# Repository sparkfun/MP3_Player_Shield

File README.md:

SparkFun MP3 Player Shield
==========================

[*SparkFun MP3 Player Shield (DEV-2660)*](https://www.sparkfun.com/products/12660)

The MP3 Player Shield has a microSD socket, VS1053 decoder IC and all the supporting circuitry to be able to decode and play MP3s from an Arduino.

Repository Contents
-------------------

* **/Documentation** - Data sheets, additional product information
* **/Firmware** - Multiple examples of how to read MP3 files and send them to the VS1053.
* **/Hardware** - All Eagle design files (.brd, .sch)
* **/Production** - Production panel files (.brd)

Documentation
--------------
* **[Hookup Guide](https://learn.sparkfun.com/tutorials/mp3-player-shield-hookup-guide-v15)** - Basic hookup guide for the Mp3 Shield.
* **[SparkFun Fritzing repo](https://github.com/sparkfun/Fritzing_Parts)** - Fritzing diagrams for SparkFun products.
* **[SparkFun 3D Model repo](https://github.com/sparkfun/3D_Models)** - 3D models of SparkFun products. 

Product Versions
----------------
* [DEV-09736](https://www.sparkfun.com/products/retired/9736)- Version 1.0. Retired. 
* [DEV-10628](https://www.sparkfun.com/products/retired/10628)- Version 1.3. Retired. 
* [DEV-12660](https://www.sparkfun.com/products/12660) - Version 1.5. Current. 

Version History
---------------
* [v1.3](https://github.com/sparkfun/MP3_Player_Shield/tree/V_1.3) - Version 1.3 GitHub files. Retired. 
* [v1.5](https://github.com/sparkfun/MP3_Player_Shield/tree/V_1.5) - Version 1.5 GitHub files. Current. 

License Information
-------------------

This product is _**open source**_! 

Please review the LICENSE.md file for license information. 

If you have any questions or concerns on licensing, please contact techsupport@sparkfun.com.

Distributed as-is; no warranty is given.

- Your friends at SparkFun.

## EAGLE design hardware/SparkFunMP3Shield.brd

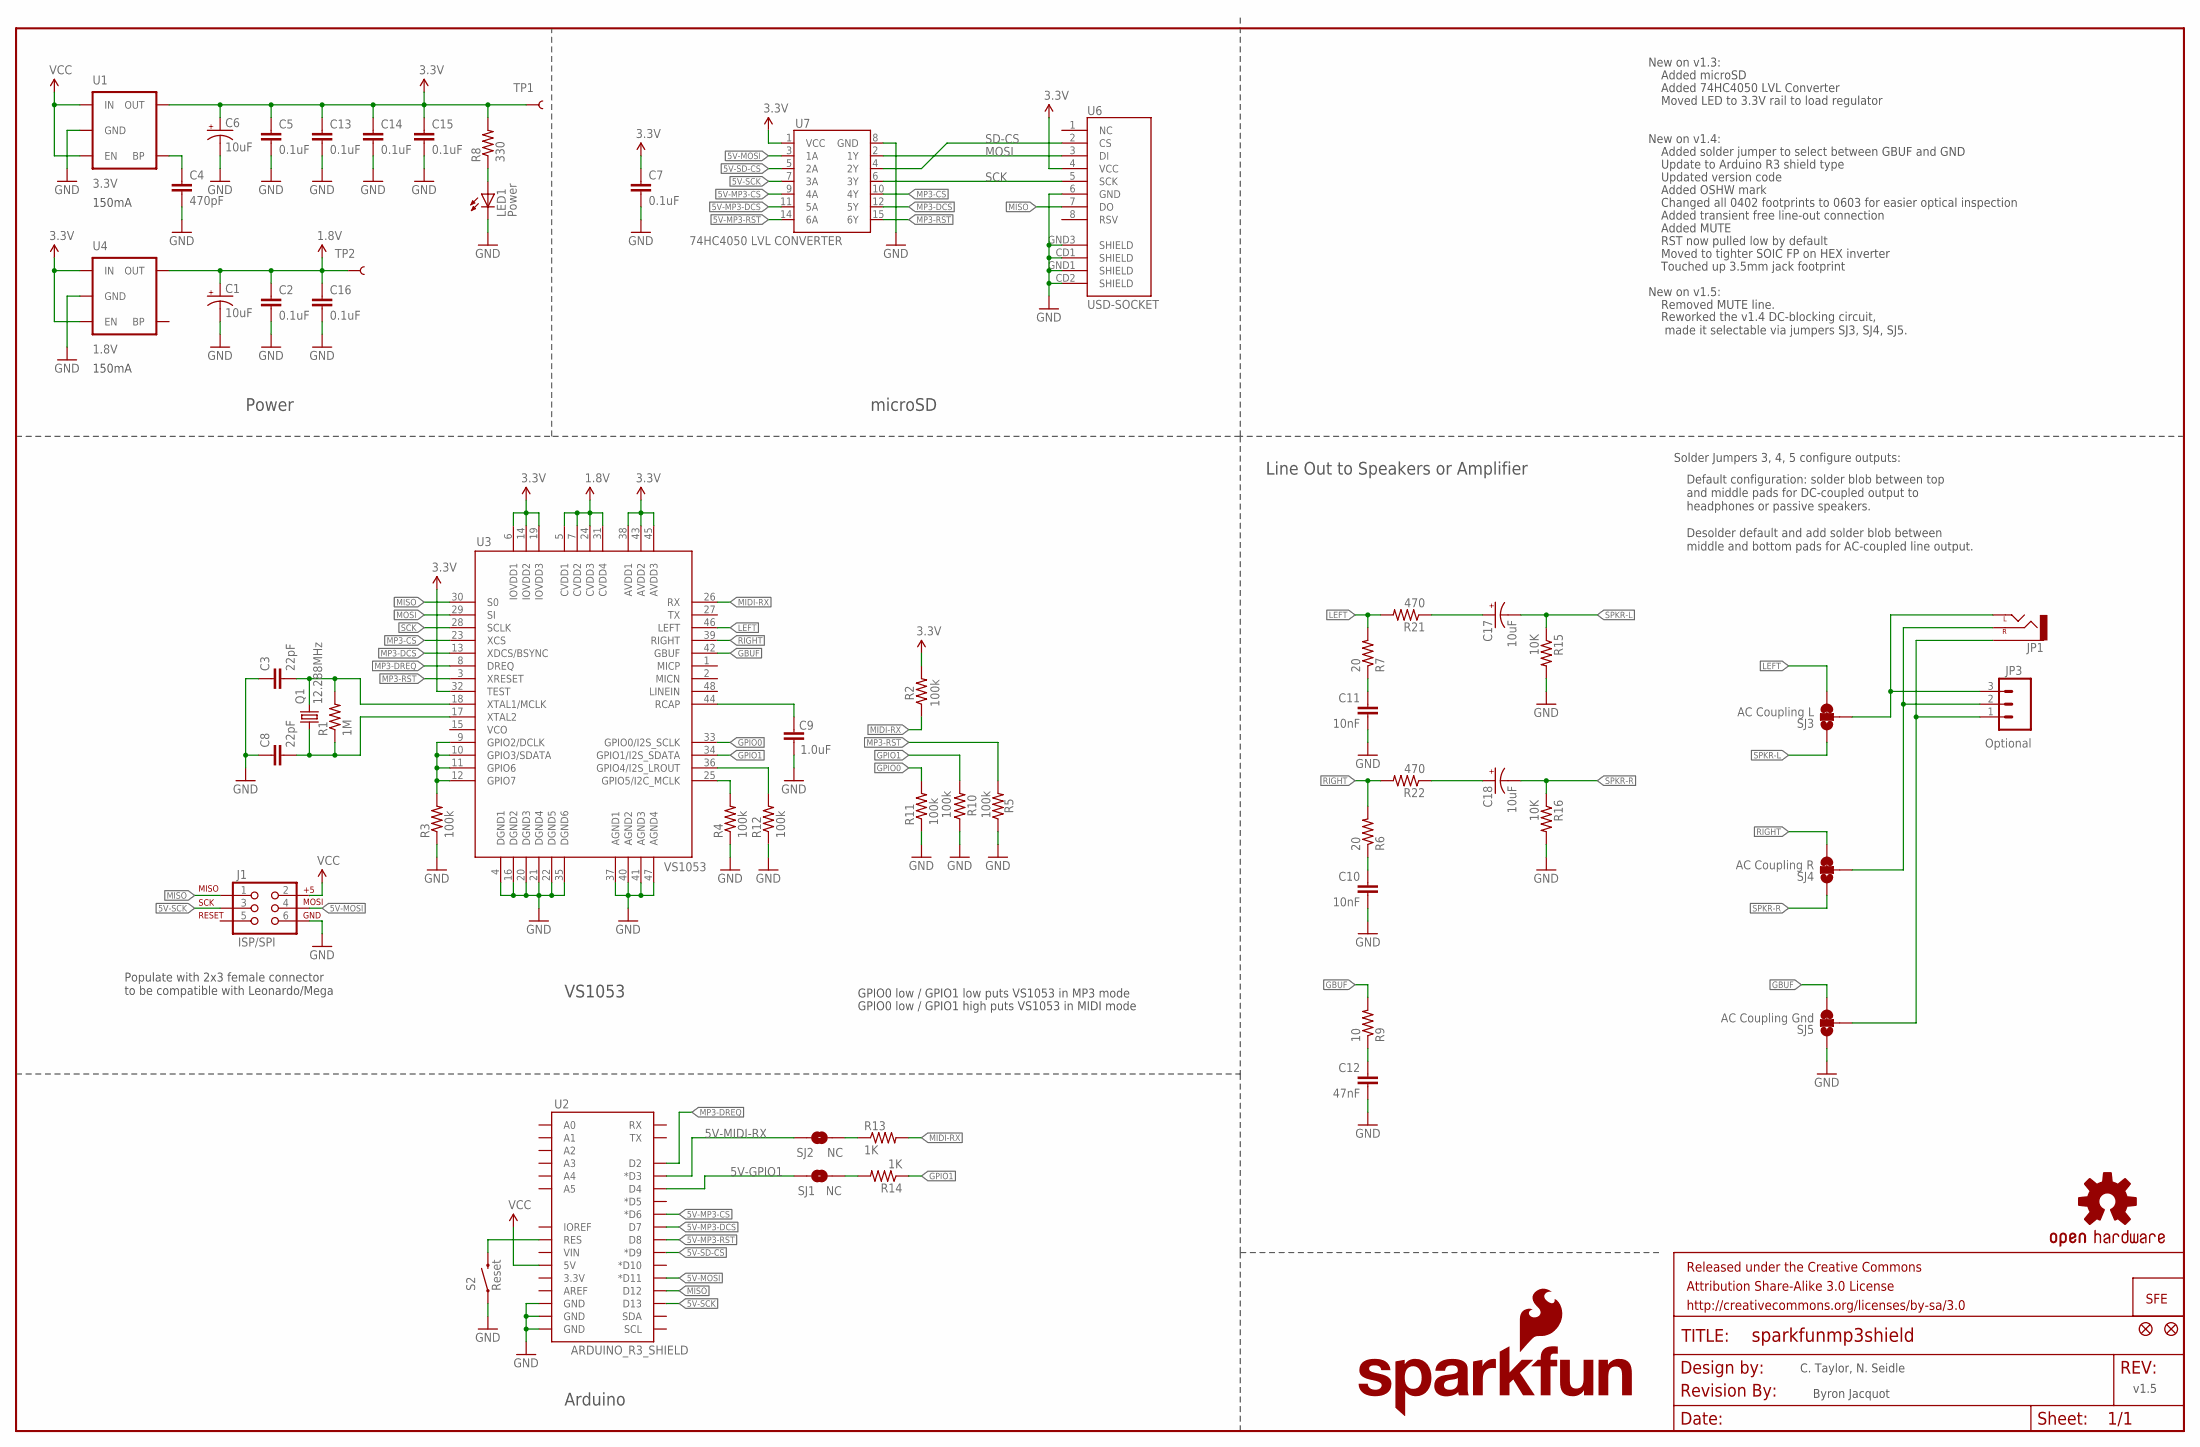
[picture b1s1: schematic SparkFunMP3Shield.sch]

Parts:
C1, C6, C17, C18: 10uF; EIA3216
C2, C5, C7, C13, C14, C15, C16: 0.1uF; 0603-CAP
C3, C8: 22pF; 0603-CAP
C4: 470pF; 0603-CAP
C9: 1.0uF; 0603-CAP
C10, C11: 10nF; 0603-CAP
C12: 47nF; 0603-CAP
FRAME1: FRAME-LEDGER; CREATIVE_COMMONS
J1: ISP/SPI; 2X3
JP1: AUDIO-JACKSMD2; AUDIO-JACK-3.5MM-SMD
JP3: Optional; 1X03
LED1: Power; LED-0603
LOGO1: OSHW-LOGOS; OSHW-LOGO-S
LOGO2: SFE_LOGO_NAME_FLAME.1_INCH; SFE_LOGO_NAME_FLAME_.1
Q1: 12.288MHz; CRYSTAL-SMD-5X3
R1: 1M; 0603-RES
R2, R3, R4, R5, R10, R11, R12: 100k; 0603-RES
R6, R7: 20; 0603-RES
R8: 330; 0603-RES
R9: 10; 0603-RES
R13, R14: 1K; 0603-RES
R15, R16: 10K; 0603-RES
R21, R22: 470; 0603-RES
S2: Reset; TACTILE_SWITCH_SMD
SJ1, SJ2: NC; SJ_2S-TRACE
SJ3: AC Coupling L; SMT-JUMPER_3_1-NC_TRACE_SILK
SJ4: AC Coupling R; SMT-JUMPER_3_1-NC_TRACE_SILK
SJ5: AC Coupling Gnd; SMT-JUMPER_3_1-NC_TRACE_SILK
TP1, TP2: TEST-POINT3X5; PAD.03X.05
U1: 3.3V; SOT23-5
U2: ARDUINO_R3_SHIELD; UNO_R3_SHIELD
U3: VS1053; LQFP-48
U4: 1.8V; SC70
U6: USD-SOCKET; MICRO-SD-SOCKET-PP
U7: 74HC4050 LVL CONVERTER; SO016
U$1: REVISION
U$4, U$5: FIDUCIAL1X2; FIDUCIAL-1X2
U$8: LOGO-SFENEW; SFE-NEW-WEBLOGO

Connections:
1.8V: C1.A (+), C2.1, C16.1, TP2.P$1, U3.5 (CVDD1), U3.7 (CVDD2), U3.24 (CVDD3), U3.31 (CVDD4), U4.5 (OUT)
3.3V: C5.1, C6.A (+), C7.1, C13.1, C14.1, C15.1, R2.2, R8.2, TP1.P$1, U1.5 (OUT), U3.6 (IOVDD1), U3.14 (IOVDD2), U3.19 (IOVDD3), U3.32 (TEST), U3.38 (AVDD1), U3.43 (AVDD2), U3.45 (AVDD3), U4.1 (IN), U4.3 (EN), U6.4 (VCC), U7.1 (VCC)
5V-GPIO1: SJ1.2, U2.D4
5V-MIDI-RX: SJ2.1, U2.D3 (*D3)
5V-MOSI: J1.4, U2.D11 (*D11), U7.3 (1A)
5V-MP3-CS: U2.D6 (*D6), U7.9 (4A)
5V-MP3-DCS: U2.D7, U7.11 (5A)
5V-MP3-RST: U2.D8, U7.14 (6A)
5V-SCK: J1.3, U2.D13, U7.7 (3A)
5V-SD-CS: U2.D9 (*D9), U7.5 (2A)
ARST: S2.3 (2), U2.RES
G1: R3.2, U3.9 (GPIO2/DCLK), U3.10 (GPIO3/SDATA), U3.11 (GPIO6), U3.12 (GPIO7)
G2: R4.2, U3.25 (GPIO5/I2C_MCLK)
GBUF: R9.2, SJ5.3, U3.42 (GBUF)
GND: C1.C (-), C2.2, C3.1, C4.2, C5.2, C6.C (-), C7.2, C8.1, C9.1, C10.2, C11.2, C12.2, C13.2, C14.2, C15.2, C16.2, J1.6, LED1.C, R3.1, R4.1, R5.1, R10.1, R11.1, R12.1, R15.2, R16.2, S2.1, SJ5.1, U1.2 (GND), U2.GND@0 (GND), U2.GND@1 (GND), U2.GND@2 (GND), U3.4 (DGND1), U3.16 (DGND2), U3.20 (DGND3), U3.21 (DGND4), U3.22 (DGND5), U3.35 (DGND6), U3.37 (AGND1), U3.40 (AGND2), U3.41 (AGND3), U3.47 (AGND4), U4.2 (GND), U6.6 (GND), U6.CD1 (SHIELD), U6.CD2 (SHIELD), U6.GND1 (SHIELD), U6.GND3 (SHIELD), U7.8 (GND)
GPIO0: R11.2, U3.33 (GPIO0/I2S_SCLK)
GPIO1: R10.2, R14.1, U3.34 (GPIO1/I2S_SDATA)
GPIO4: R12.2, U3.36 (GPIO4/I2S_LROUT)
LEFT: R7.2, R21.2, SJ3.3, U3.46 (LEFT)
MIDI-RX: R2.1, R13.2, U3.26 (RX)
MISO: J1.1, U2.D12, U3.30 (S0), U6.7 (DO)
MOSI: U3.29 (SI), U6.3 (DI), U7.2 (1Y)
MP3-CS: U3.23 (XCS), U7.10 (4Y)
MP3-DCS: U3.13 (XDCS/BSYNC), U7.12 (5Y)
MP3-DREQ: U2.D2, U3.8 (DREQ)
MP3-RST: R5.2, U3.3 (XRESET), U7.15 (6Y)
unnamed: C12.1, R9.1
unnamed: C10.1, R6.1
unnamed: R14.2, SJ1.1
unnamed: C11.1, R7.1
unnamed: LED1.A, R8.1
unnamed: R13.1, SJ2.2
unnamed: C3.2, Q1.3 (2), R1.2, U3.18 (XTAL1/MCLK)
unnamed: C8.2, Q1.1, R1.1, U3.17 (XTAL2)
unnamed: JP1.SLEEVE, JP3.1, SJ5.2
unnamed: JP1.RING (RIGHT), JP3.2, SJ4.2
unnamed: JP1.TIP (LEFT), JP3.3, SJ3.2
unnamed: C18.A (+), R22.1
unnamed: C17.A (+), R21.1
unnamed: C4.1, U1.4 (BP)
RCAP: C9.2, U3.44 (RCAP)
RIGHT: R6.2, R22.2, SJ4.3, U3.39 (RIGHT)
SCK: U3.28 (SCLK), U6.5 (SCK), U7.6 (3Y)
SD-CS: U6.2 (CS), U7.4 (2Y)
SPKR-L: C17.C (-), R15.1, SJ3.1
SPKR-R: C18.C (-), R16.1, SJ4.1
VCC: J1.2, U1.1 (IN), U1.3 (EN), U2.5V

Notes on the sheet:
GPIO0 low / GPIO1 high puts VS1053 in MIDI mode
C. Taylor, N. Seidle
New on v1.3:
GPIO0 low / GPIO1 low puts VS1053 in MP3 mode
microSD
Power
Line Out to Speakers or Amplifier
Arduino
VS1053
Moved LED to 3.3V rail to load regulator
Added microSD
Added 74HC4050 LVL Converter
New on v1.4:
Added solder jumper to select between GBUF and GND
Default configuration: solder blob between top and middle pads for DC-coupled output to headphones or passive speakers. Desolder default and add solder blob between middle and bottom pads for AC-coupled line output.
Update to Arduino R3 shield type
Updated version code
Added OSHW mark
Changed all 0402 footprints to 0603 for easier optical inspection
Added transient free line-out connection
Added MUTE
Solder Jumpers 3, 4, 5 configure outputs:
150mA
v1.5
RST now pulled low by default
Populate with 2x3 female connector to be compatible with Leonardo/Mega
Moved to tighter SOIC FP on HEX inverter
Touched up 3.5mm jack footprint
Byron Jacquot
New on v1.5:
Removed MUTE line.
Reworked the v1.4 DC-blocking circuit, made it selectable via jumpers SJ3, SJ4, SJ5.

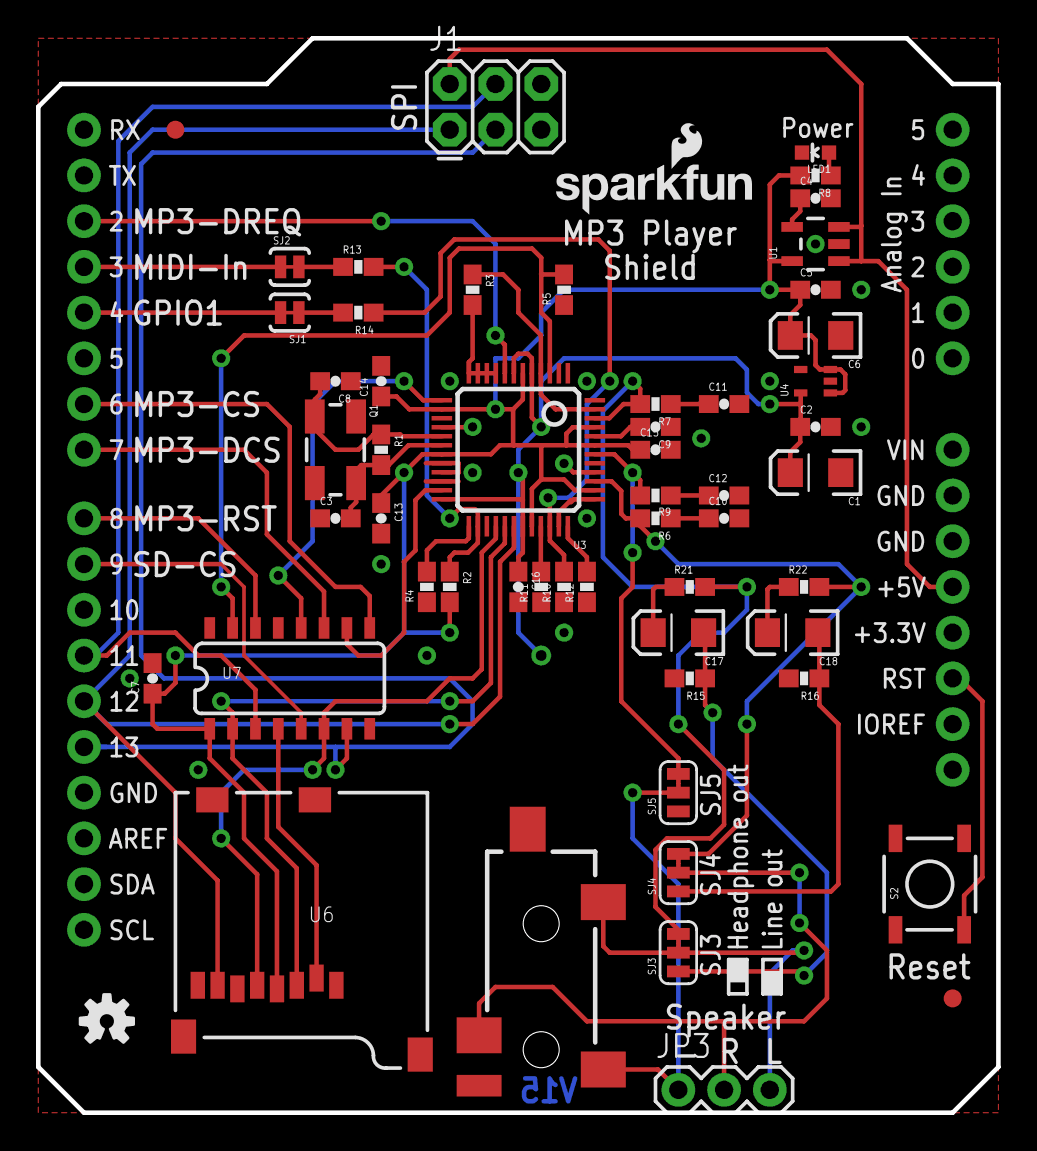
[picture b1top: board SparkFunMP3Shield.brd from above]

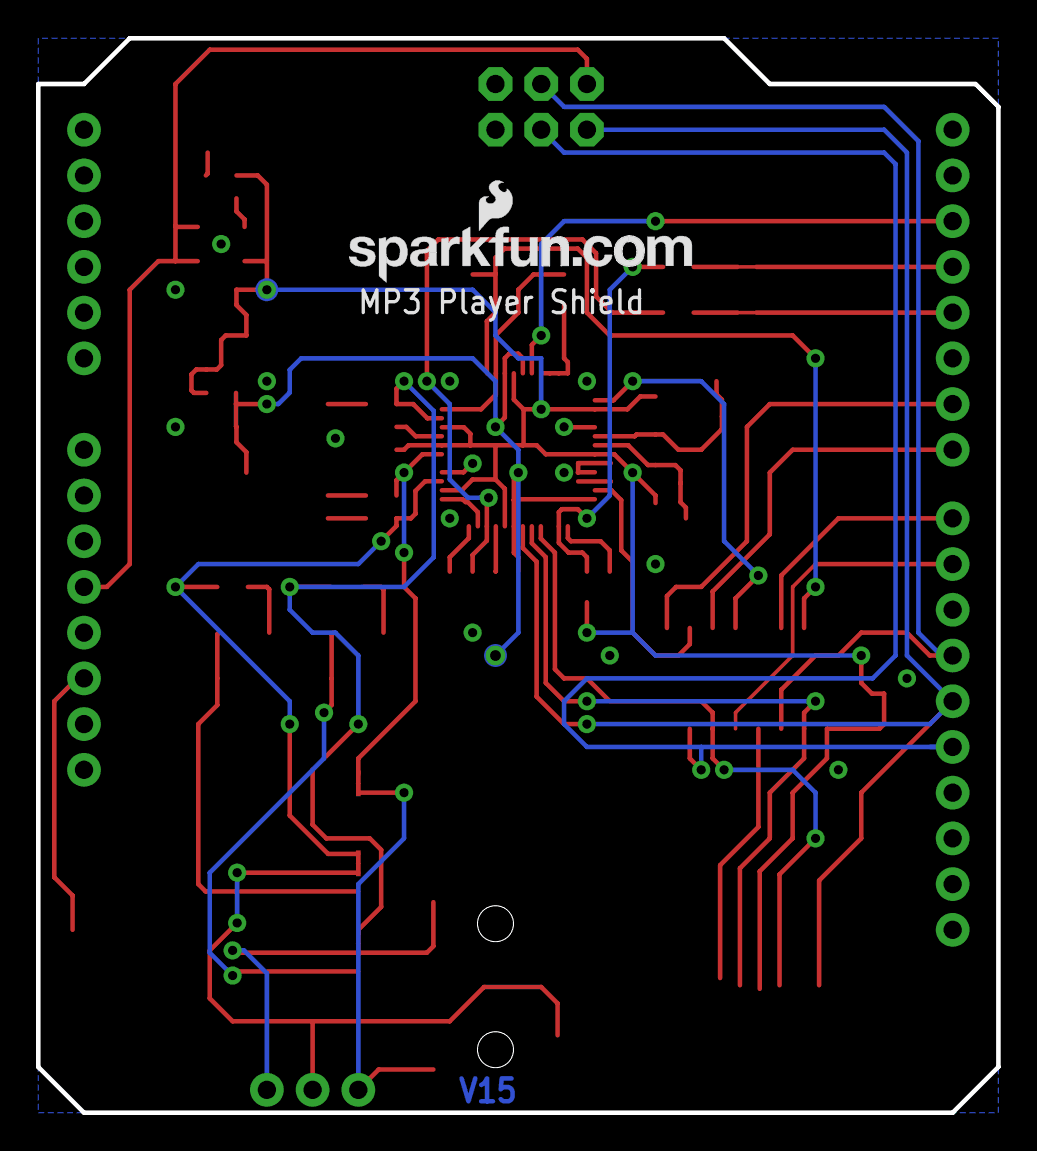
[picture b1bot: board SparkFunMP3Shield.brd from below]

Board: 2 copper layers, 53.3 x 59.7 mm, 62 parts (3 on the bottom side), 47 nets.

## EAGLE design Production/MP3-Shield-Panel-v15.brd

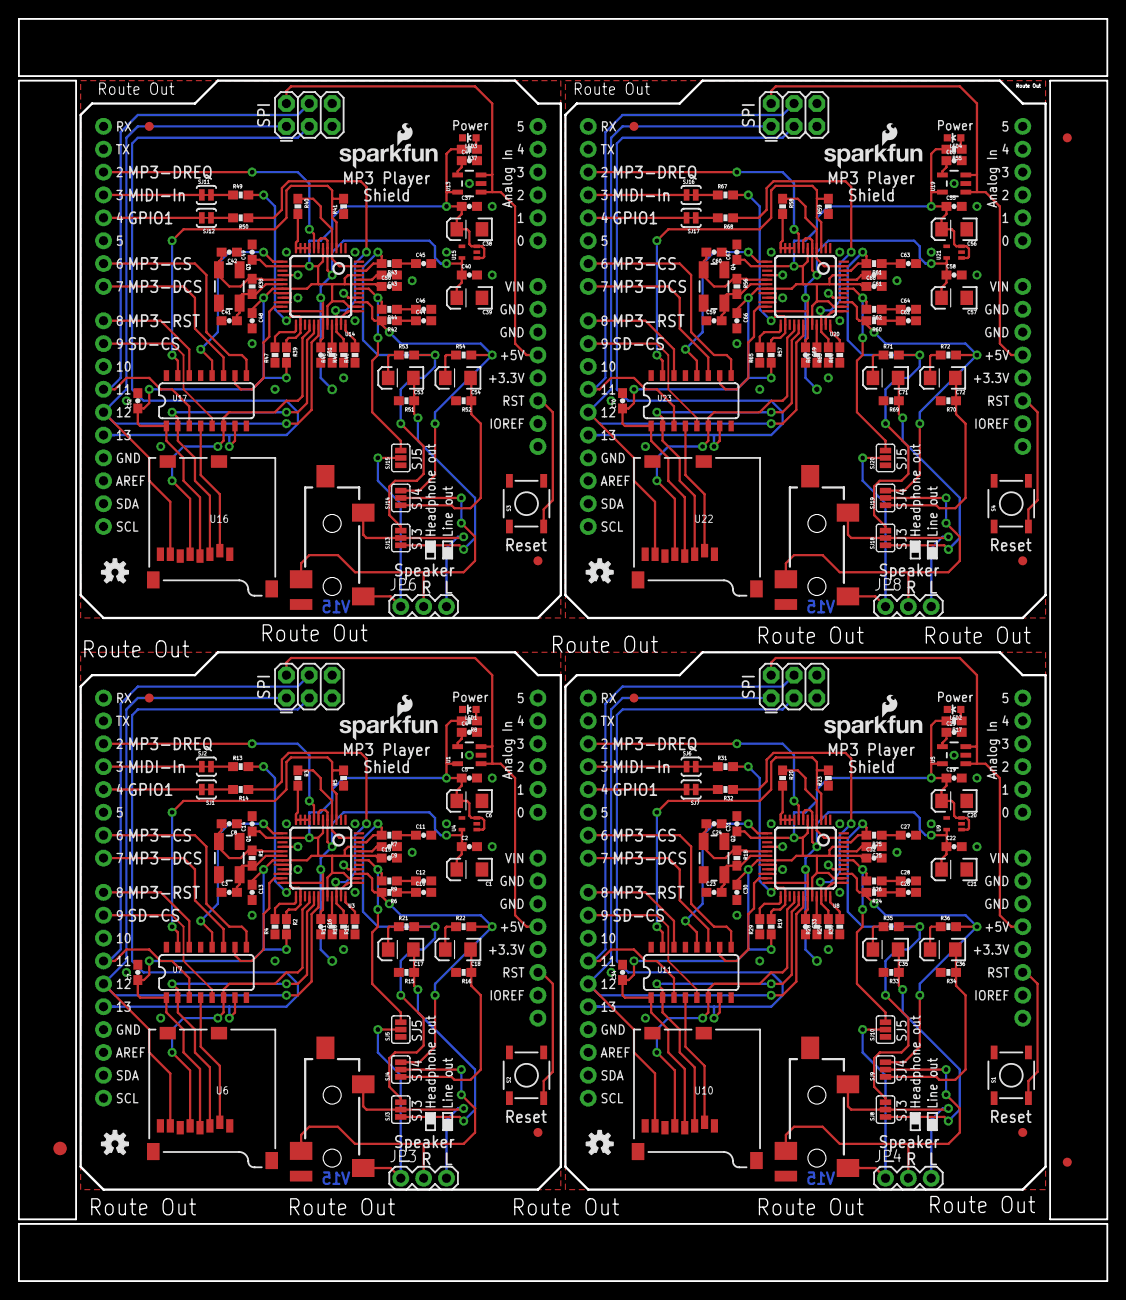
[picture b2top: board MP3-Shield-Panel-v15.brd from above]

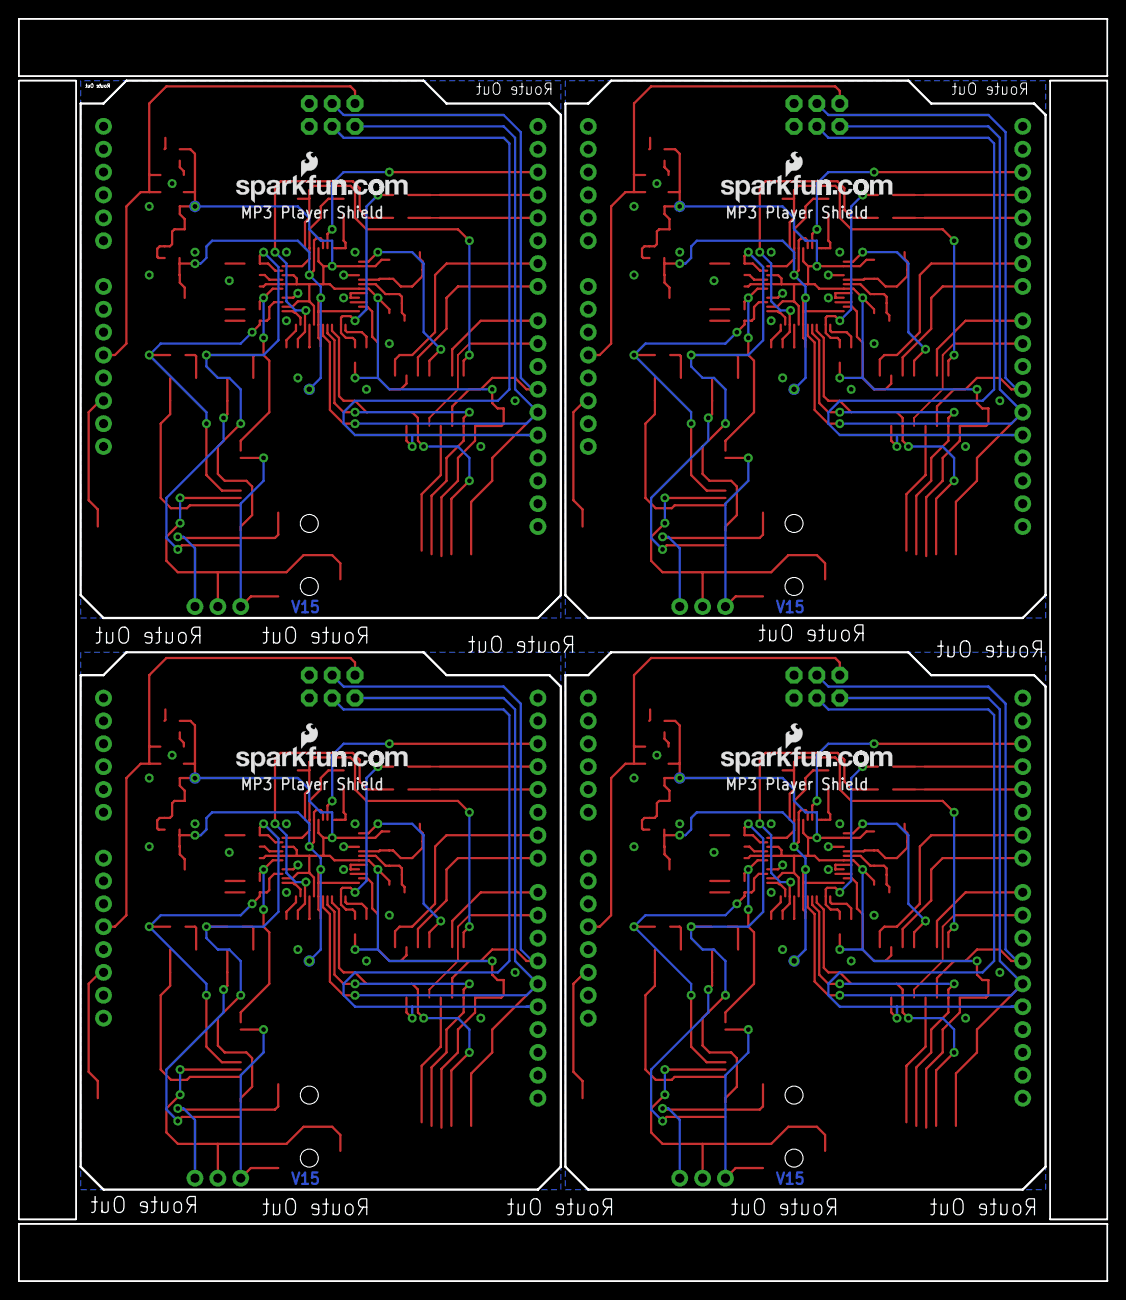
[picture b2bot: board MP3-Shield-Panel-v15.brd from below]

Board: 2 copper layers, 120.9 x 140.2 mm, 243 parts (12 on the bottom side), 188 nets.

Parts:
C1, C6, C17, C18, C20, C21, C35, C36, C38, C39, C53, C54, C56, C57, C71, C72: 10uF; EIA3216
C2, C5, C7, C13, C14, C15, C16, C19, C22, C30, C31, C32, C33, C34, C37, C40, C48, C49, C50, C51, C52, C55, C58, C66, C67, C68, C69, C70: 0.1uF; 0603-CAP
C3, C8, C23, C24, C41, C42, C59, C60: 22pF; 0603-CAP
C4, C29, C47, C65: 470pF; 0603-CAP
C9, C25, C43, C61: 1.0uF; 0603-CAP
C10, C11, C26, C27, C44, C45, C62, C63: 10nF; 0603-CAP
C12, C28, C46, C64: 47nF; 0603-CAP
E$1: FIDUCIAL-1.5X3
E$4, E$5: FIDUCIAL-1X2
J1, J2, J3, J4: ISP/SPI; 2X3
JP1, JP2, JP5, JP7: AUDIO-JACK-3.5MM-SMD
JP3, JP4, JP6, JP8: Optional; 1X03
LED1, LED2, LED3, LED4: Power; LED-0603
LOGO1, LOGO3, LOGO5, LOGO7: OSHW-LOGOS; OSHW-LOGO-S
LOGO2, LOGO4, LOGO6, LOGO8: SFE_LOGO_NAME_FLAME.1_INCH; SFE_LOGO_NAME_FLAME_.1
Q1, Q2, Q3, Q4: 12.288MHz; CRYSTAL-SMD-5X3
R1, R18, R38, R56: 1M; 0603-RES
R2, R3, R4, R5, R10, R11, R12, R19, R20, R23, R27, R28, R29, R30, R39, R40, R41, R45, R46, R47, R48, R57, R58, R59, R63, R64, R65, R66: 100k; 0603-RES
R6, R7, R24, R25, R42, R43, R60, R61: 20; 0603-RES
R8, R17, R37, R55: 330; 0603-RES
R9, R26, R44, R62: 10; 0603-RES
R13, R14, R31, R32, R49, R50, R67, R68: 1K; 0603-RES
R15, R16, R33, R34, R51, R52, R69, R70: 10K; 0603-RES
R21, R22, R35, R36, R53, R54, R71, R72: 470; 0603-RES
S1, S2, S3, S4: Reset; TACTILE_SWITCH_SMD
SJ1, SJ2, SJ6, SJ7, SJ11, SJ12, SJ16, SJ17: NC; SJ_2S-TRACE
SJ3, SJ8, SJ13, SJ18: AC Coupling L; PAD-JUMPER-3-2OF3_NC_BY_PASTE_YES_SILK_FULL_BOX
SJ4, SJ9, SJ14, SJ19: AC Coupling R; PAD-JUMPER-3-2OF3_NC_BY_PASTE_YES_SILK_FULL_BOX
SJ5, SJ10, SJ15, SJ20: AC Coupling Gnd; PAD-JUMPER-3-2OF3_NC_BY_PASTE_YES_SILK_FULL_BOX
TP1, TP2, TP3, TP4, TP5, TP6, TP7, TP8: PAD.03X.05
U1, U5, U13, U19: 3.3V; SOT23-5
U2, U12, U18, U24: ARDUINO_R3_SHIELD; UNO_R3_SHIELD
U3, U8, U14, U20: VS1053; LQFP-48
U4, U9, U15, U21: 1.8V; SC70
U6, U10, U16, U22: USD-SOCKET; MICRO-SD-SOCKET-PP
U7, U11, U17, U23: 74HC4050 LVL CONVERTER; SO016
U$1, U$2, U$4, U$5, U$6, U$7, U$10, U$11: FIDUCIAL1X2; FIDUCIAL-1X2
U$3, U$8, U$9, U$12: LOGO-SFENEW; SFE-NEW-WEBLOGO

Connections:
1.8V: C1.A, C2.1, C16.1, TP2.P$1, U3.5, U3.7, U3.24, U3.31, U4.5
1.8V1: C21.A, C22.1, C33.1, TP4.P$1, U8.5, U8.7, U8.24, U8.31, U9.5
1.8V2: C39.A, C40.1, C51.1, TP6.P$1, U14.5, U14.7, U14.24, U14.31, U15.5
1.8V3: C57.A, C58.1, C69.1, TP8.P$1, U20.5, U20.7, U20.24, U20.31, U21.5
3.3V: C5.1, C6.A, C7.1, C13.1, C14.1, C15.1, R2.2, R8.2, TP1.P$1, U1.5, U3.6, U3.14, U3.19, U3.32, U3.38, U3.43, U3.45, U4.1, U4.3, U6.4, U7.1
3.3V1: C19.1, C20.A, C30.1, C31.1, C32.1, C34.1, R17.2, R19.2, TP3.P$1, U5.5, U8.6, U8.14, U8.19, U8.32, U8.38, U8.43, U8.45, U9.1, U9.3, U10.4, U11.1
3.3V2: C37.1, C38.A, C48.1, C49.1, C50.1, C52.1, R37.2, R39.2, TP5.P$1, U13.5, U14.6, U14.14, U14.19, U14.32, U14.38, U14.43, U14.45, U15.1, U15.3, U16.4, U17.1
3.3V3: C55.1, C56.A, C66.1, C67.1, C68.1, C70.1, R55.2, R57.2, TP7.P$1, U19.5, U20.6, U20.14, U20.19, U20.32, U20.38, U20.43, U20.45, U21.1, U21.3, U22.4, U23.1
5V-GPIO1: SJ1.2, U2.D4
5V-GPIO2: SJ7.2, U12.D4
5V-GPIO3: SJ12.2, U18.D4
5V-GPIO4: SJ17.2, U24.D4
5V-MIDI-RX: SJ2.1, U2.D3
5V-MIDI-RX1: SJ6.1, U12.D3
5V-MIDI-RX2: SJ11.1, U18.D3
5V-MIDI-RX3: SJ16.1, U24.D3
5V-MOSI: J1.4, U2.D11, U7.3
5V-MOSI1: J2.4, U11.3, U12.D11
5V-MOSI2: J3.4, U17.3, U18.D11
5V-MOSI3: J4.4, U23.3, U24.D11
5V-MP3-CS: U2.D6, U7.9
5V-MP3-CS1: U11.9, U12.D6
5V-MP3-CS2: U17.9, U18.D6
5V-MP3-CS3: U23.9, U24.D6
5V-MP3-DCS: U2.D7, U7.11
5V-MP3-DCS1: U11.11, U12.D7
5V-MP3-DCS2: U17.11, U18.D7
5V-MP3-DCS3: U23.11, U24.D7
5V-MP3-RST: U2.D8, U7.14
5V-MP3-RST1: U11.14, U12.D8
5V-MP3-RST2: U17.14, U18.D8
5V-MP3-RST3: U23.14, U24.D8
5V-SCK: J1.3, U2.D13, U7.7
5V-SCK1: J2.3, U11.7, U12.D13
5V-SCK2: J3.3, U17.7, U18.D13
5V-SCK3: J4.3, U23.7, U24.D13
5V-SD-CS: U2.D9, U7.5
5V-SD-CS1: U11.5, U12.D9
5V-SD-CS2: U17.5, U18.D9
5V-SD-CS3: U23.5, U24.D9
ARST: S2.3, U2.RES
ARST1: S1.3, U12.RES
ARST2: S3.3, U18.RES
ARST3: S4.3, U24.RES
G1: R3.2, U3.9, U3.10, U3.11, U3.12
G2: R4.2, U3.25
G3: R20.2, U8.9, U8.10, U8.11, U8.12
G4: R29.2, U8.25
G5: R40.2, U14.9, U14.10, U14.11, U14.12
G6: R47.2, U14.25
G7: R58.2, U20.9, U20.10, U20.11, U20.12
G8: R65.2, U20.25
GBUF: R9.2, SJ5.3, U3.42
GBUF1: R26.2, SJ10.3, U8.42
GBUF2: R44.2, SJ15.3, U14.42
GBUF3: R62.2, SJ20.3, U20.42
GND: C1.C, C2.2, C3.1, C4.2, C5.2, C6.C, C7.2, C8.1, C9.1, C10.2, C11.2, C12.2, C13.2, C14.2, C15.2, C16.2, J1.6, LED1.C, R3.1, R4.1, R5.1, R10.1, R11.1, R12.1, R15.2, R16.2, S2.1, SJ5.1, U1.2, U2.GND@0, U2.GND@1, U2.GND@2, U3.4, U3.16, U3.20, U3.21, U3.22, U3.35, U3.37, U3.40, U3.41, U3.47, U4.2, U6.6, U6.CD1, U6.CD2, U6.GND1, U6.GND3, U7.8
GND1: C19.2, C20.C, C21.C, C22.2, C23.1, C24.1, C25.1, C26.2, C27.2, C28.2, C29.2, C30.2, C31.2, C32.2, C33.2, C34.2, J2.6, LED2.C, R20.1, R23.1, R27.1, R28.1, R29.1, R30.1, R33.2, R34.2, S1.1, SJ10.1, U5.2, U8.4, U8.16, U8.20, U8.21, U8.22, U8.35, U8.37, U8.40, U8.41, U8.47, U9.2, U10.6, U10.CD1, U10.CD2, U10.GND1, U10.GND3, U11.8, U12.GND@0, U12.GND@1, U12.GND@2
GND2: C37.2, C38.C, C39.C, C40.2, C41.1, C42.1, C43.1, C44.2, C45.2, C46.2, C47.2, C48.2, C49.2, C50.2, C51.2, C52.2, J3.6, LED3.C, R40.1, R41.1, R45.1, R46.1, R47.1, R48.1, R51.2, R52.2, S3.1, SJ15.1, U13.2, U14.4, U14.16, U14.20, U14.21, U14.22, U14.35, U14.37, U14.40, U14.41, U14.47, U15.2, U16.6, U16.CD1, U16.CD2, U16.GND1, U16.GND3, U17.8, U18.GND@0, U18.GND@1, U18.GND@2
GND3: C55.2, C56.C, C57.C, C58.2, C59.1, C60.1, C61.1, C62.2, C63.2, C64.2, C65.2, C66.2, C67.2, C68.2, C69.2, C70.2, J4.6, LED4.C, R58.1, R59.1, R63.1, R64.1, R65.1, R66.1, R69.2, R70.2, S4.1, SJ20.1, U19.2, U20.4, U20.16, U20.20, U20.21, U20.22, U20.35, U20.37, U20.40, U20.41, U20.47, U21.2, U22.6, U22.CD1, U22.CD2, U22.GND1, U22.GND3, U23.8, U24.GND@0, U24.GND@1, U24.GND@2
GPIO0: R11.2, U3.33
GPIO1: R10.2, R14.1, U3.34
GPIO2: R28.2, U8.33
GPIO3: R27.2, R32.1, U8.34
GPIO4: R12.2, U3.36
GPIO5: R30.2, U8.36
GPIO6: R46.2, U14.33
GPIO7: R45.2, R50.1, U14.34
GPIO8: R48.2, U14.36
GPIO9: R64.2, U20.33
GPIO10: R63.2, R68.1, U20.34
GPIO11: R66.2, U20.36
LEFT: R7.2, R21.2, SJ3.3, U3.46
LEFT1: R25.2, R35.2, SJ8.3, U8.46
LEFT2: R43.2, R53.2, SJ13.3, U14.46
LEFT3: R61.2, R71.2, SJ18.3, U20.46
MIDI-RX: R2.1, R13.2, U3.26
MIDI-RX1: R19.1, R31.2, U8.26
MIDI-RX2: R39.1, R49.2, U14.26
MIDI-RX3: R57.1, R67.2, U20.26
MISO: J1.1, U2.D12, U3.30, U6.7
MISO1: J2.1, U8.30, U10.7, U12.D12
MISO2: J3.1, U14.30, U16.7, U18.D12
MISO3: J4.1, U20.30, U22.7, U24.D12
MOSI: U3.29, U6.3, U7.2
MOSI1: U8.29, U10.3, U11.2
MOSI2: U14.29, U16.3, U17.2
MOSI3: U20.29, U22.3, U23.2
MP3-CS: U3.23, U7.10
MP3-CS1: U8.23, U11.10
MP3-CS2: U14.23, U17.10
MP3-CS3: U20.23, U23.10
MP3-DCS: U3.13, U7.12
MP3-DCS1: U8.13, U11.12
MP3-DCS2: U14.13, U17.12
MP3-DCS3: U20.13, U23.12
MP3-DREQ: U2.D2, U3.8
MP3-DREQ1: U8.8, U12.D2
MP3-DREQ2: U14.8, U18.D2
MP3-DREQ3: U20.8, U24.D2
MP3-RST: R5.2, U3.3, U7.15
MP3-RST1: R23.2, U8.3, U11.15
MP3-RST2: R41.2, U14.3, U17.15
MP3-RST3: R59.2, U20.3, U23.15
unnamed: LED2.A, R17.1
unnamed: C12.1, R9.1
unnamed: C10.1, R6.1
unnamed: R14.2, SJ1.1
unnamed: C11.1, R7.1
unnamed: LED1.A, R8.1
unnamed: C23.2, Q2.3, R18.2, U8.18
unnamed: R13.1, SJ2.2
unnamed: C3.2, Q1.3, R1.2, U3.18
unnamed: C8.2, Q1.1, R1.1, U3.17
unnamed: C24.2, Q2.1, R18.1, U8.17
unnamed: JP1.SLEEVE, JP3.1, SJ5.2
unnamed: JP1.RING, JP3.2, SJ4.2
unnamed: JP1.TIP, JP3.3, SJ3.2
unnamed: C28.1, R26.1
unnamed: C27.1, R25.1
unnamed: C18.A, R22.1
unnamed: C26.1, R24.1
unnamed: C17.A, R21.1
unnamed: C29.1, U5.4
unnamed: R31.1, SJ6.2
unnamed: R32.2, SJ7.1
unnamed: C36.A, R36.1
unnamed: C35.A, R35.1
unnamed: JP2.SLEEVE, JP4.1, SJ10.2
unnamed: JP2.RING, JP4.2, SJ9.2
unnamed: JP2.TIP, JP4.3, SJ8.2
unnamed: LED3.A, R37.1
unnamed: C41.2, Q3.3, R38.2, U14.18
unnamed: C42.2, Q3.1, R38.1, U14.17
unnamed: C46.1, R44.1
unnamed: C45.1, R43.1
unnamed: C44.1, R42.1
unnamed: C47.1, U13.4
unnamed: R49.1, SJ11.2
unnamed: R50.2, SJ12.1
unnamed: C54.A, R54.1
unnamed: C53.A, R53.1
unnamed: JP5.SLEEVE, JP6.1, SJ15.2
unnamed: JP5.RING, JP6.2, SJ14.2
unnamed: JP5.TIP, JP6.3, SJ13.2
unnamed: LED4.A, R55.1
unnamed: C59.2, Q4.3, R56.2, U20.18
unnamed: C60.2, Q4.1, R56.1, U20.17
unnamed: C64.1, R62.1
unnamed: C63.1, R61.1
unnamed: C62.1, R60.1
unnamed: C65.1, U19.4
unnamed: R67.1, SJ16.2
unnamed: R68.2, SJ17.1
unnamed: C72.A, R72.1
unnamed: C71.A, R71.1
unnamed: JP7.SLEEVE, JP8.1, SJ20.2
unnamed: JP7.RING, JP8.2, SJ19.2
unnamed: JP7.TIP, JP8.3, SJ18.2
unnamed: C4.1, U1.4
RCAP: C9.2, U3.44
RCAP1: C25.2, U8.44
RCAP2: C43.2, U14.44
RCAP3: C61.2, U20.44
RIGHT: R6.2, R22.2, SJ4.3, U3.39
RIGHT1: R24.2, R36.2, SJ9.3, U8.39
RIGHT2: R42.2, R54.2, SJ14.3, U14.39
RIGHT3: R60.2, R72.2, SJ19.3, U20.39
SCK: U3.28, U6.5, U7.6
SCK1: U8.28, U10.5, U11.6
SCK2: U14.28, U16.5, U17.6
SCK3: U20.28, U22.5, U23.6
SD-CS: U6.2, U7.4
SD-CS1: U10.2, U11.4
SD-CS2: U16.2, U17.4
SD-CS3: U22.2, U23.4
SPKR-L: C17.C, R15.1, SJ3.1
SPKR-L1: C35.C, R33.1, SJ8.1
SPKR-L2: C53.C, R51.1, SJ13.1
SPKR-L3: C71.C, R69.1, SJ18.1
SPKR-R: C18.C, R16.1, SJ4.1
SPKR-R1: C36.C, R34.1, SJ9.1
SPKR-R2: C54.C, R52.1, SJ14.1
SPKR-R3: C72.C, R70.1, SJ19.1
VCC: J1.2, U1.1, U1.3, U2.5V
VCC1: J2.2, U5.1, U5.3, U12.5V
VCC2: J3.2, U13.1, U13.3, U18.5V
VCC3: J4.2, U19.1, U19.3, U24.5V

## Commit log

2013-11-27 Initial commit at v1.3
    Repo was started at PCB date code 4-1-11.
2013-12-02 README picture and SKU update
2014-09-26 Initial commit of V1.5
    1.5 replaces 1.4.
    Very much WIP with this checkin.
2014-09-26 More WIP.
2014-09-26 Yet more WIP
2014-10-13 V1.5 ready for protos.
    Board routed and ready for protos.
2014-11-05 Ready to review for reds
    Reorganized the solder jumpers for output coupling selection.
2014-11-10 Tweaking after review
    Clarifying solder jumpers for output configuration.
2014-11-12 Updating based on QC checklist.
2014-11-17 created panel v15
2015-06-26 Updating README, adding license file, cleaning up repo structure
2015-06-26 Updating .git files
2021-12-15 Update example to use libraries.
2021-12-15 Correct CS pin to default
2024-09-27 Use traces to close jumpers

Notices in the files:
parts and their libraries:
SparkFun-Passives: Licensing: CC v3.0 Share-Alike You are welcome to use this library for commercial purposes.
SparkFun-Retired: Licensing:Creative Commons ShareAlike 4.0 International - https://creativecommons.org/licenses/by-sa/4.0
SparkFun-Aesthetics: Released under the Creative Commons
